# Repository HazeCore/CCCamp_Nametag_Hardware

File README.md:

# CCCamp 2023 Nametag Hardware

This is the hardware for out Nametag Badge for Chaos Communication Camp 2023. You can find more information about the Project at [https://hazeco.re/cccamp-nametag/](https://hazeco.re/cccamp-nametag/).

The state of the actual produced Hardware for CCCamp is tagged as version "v1.0".

This Repo contains a KiCAD Project, with all information to order the PCB or Modify it.

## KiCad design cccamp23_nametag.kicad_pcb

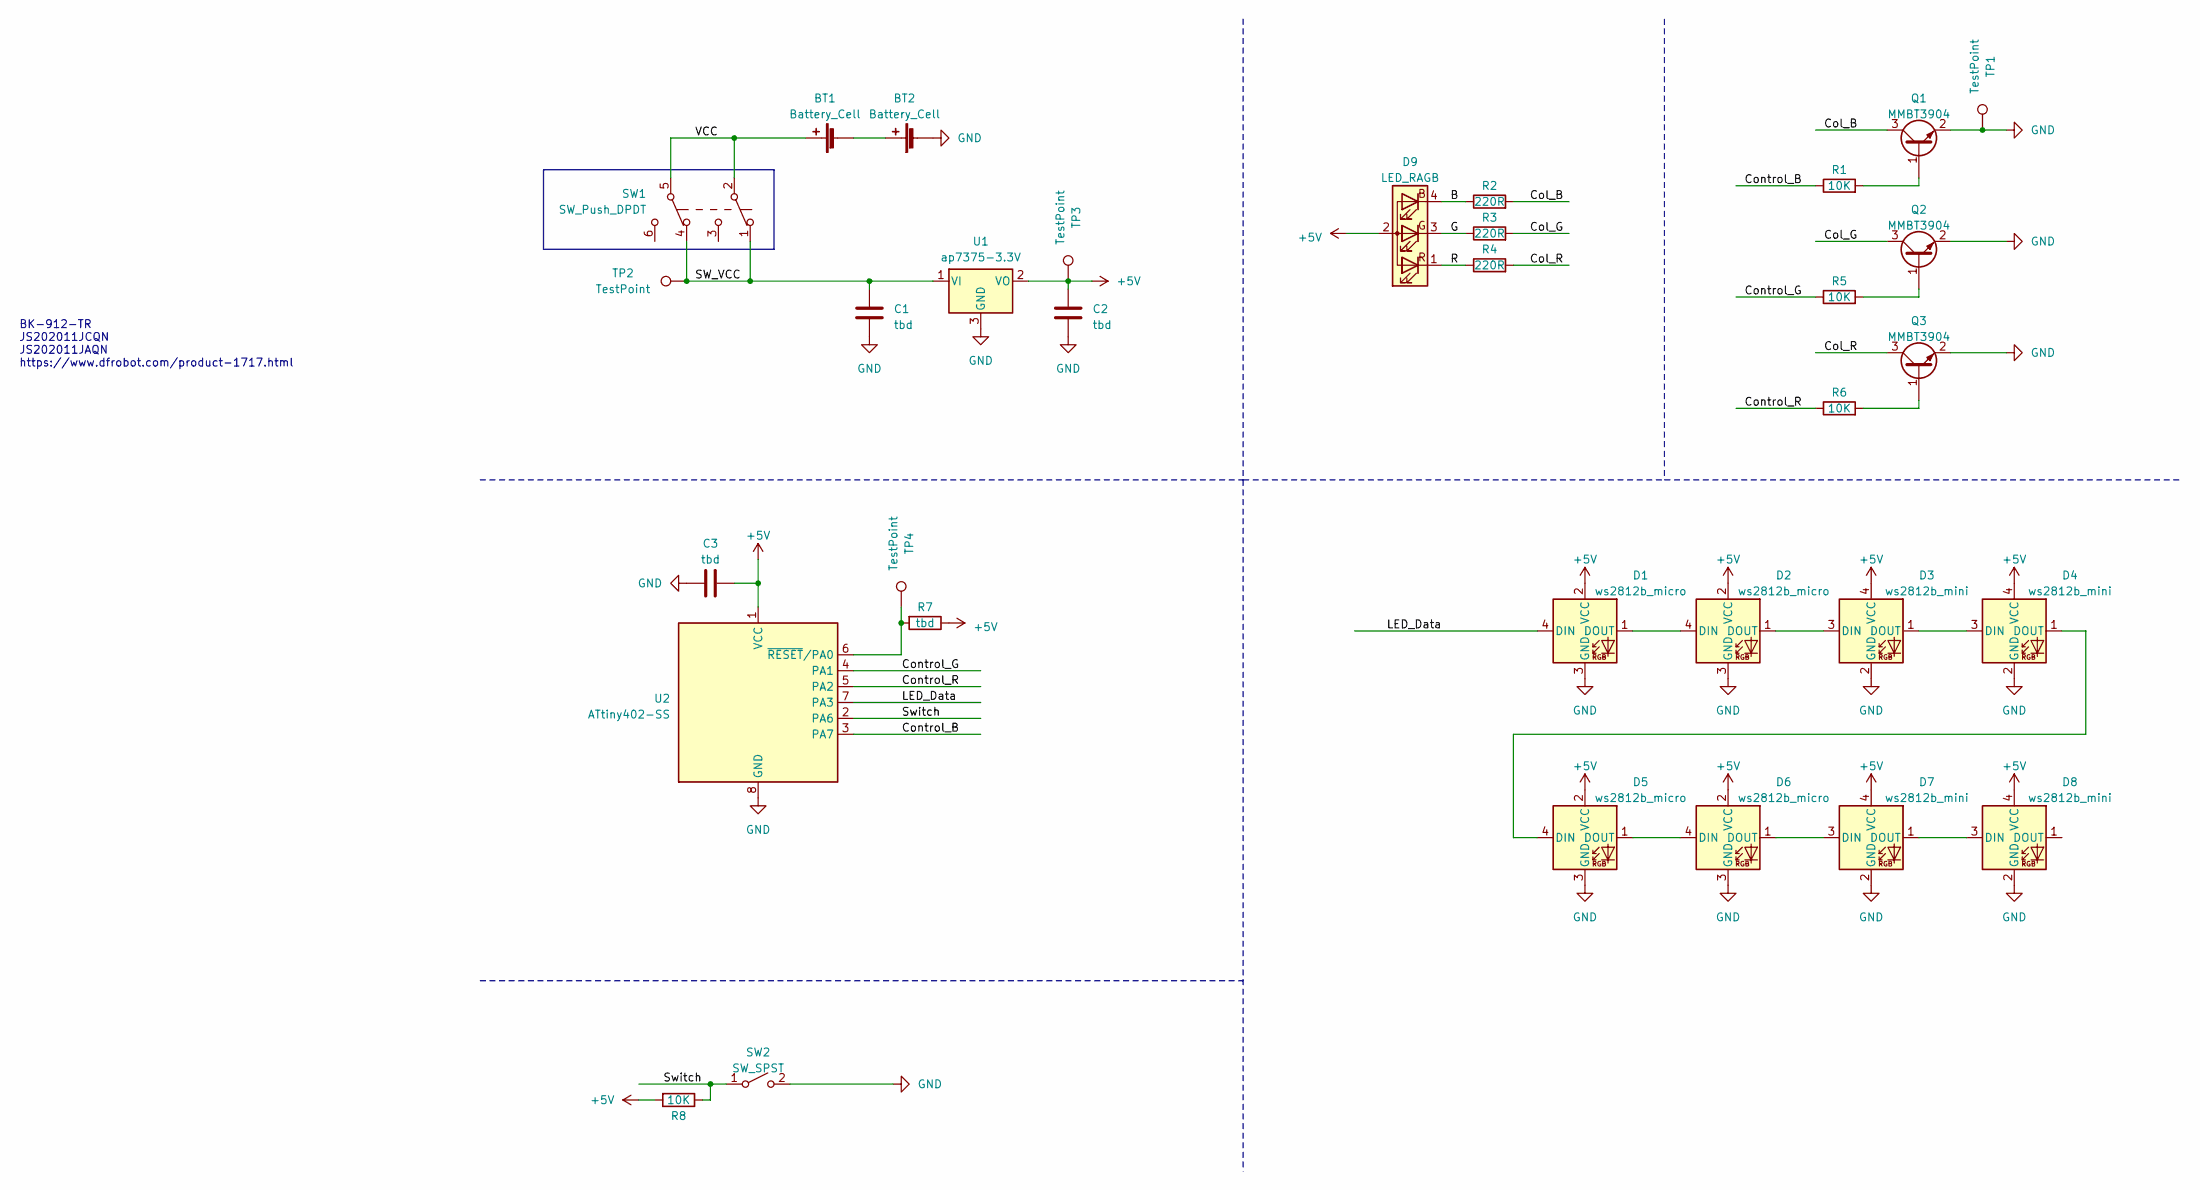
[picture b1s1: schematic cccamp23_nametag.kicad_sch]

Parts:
BT1, BT2: Battery_Cell; BatteryHolder_MPD_BC2003_1x2032
C1, C2, C3: tbd; C_0603_1608Metric
D1, D2, D5, D6: ws2812b_micro
D3, D4, D7, D8: ws2812b_mini
D9: LED_RAGB; PinHeader_1x04_P1.27mm_Vertical
Q1, Q2, Q3: MMBT3904; SOT-23
R1, R5, R6, R8: 10K; R_0603_1608Metric
R2, R3, R4: 220R; R_0603_1608Metric
R7: tbd; R_0603_1608Metric
SW1: SW_Push_DPDT; SW_DPDT_CK_JS202011JCQN
SW2: SW_SPST; pts526
TP1, TP2, TP3, TP4: TestPoint; TestPoint_Pad_D1.5mm
U1: ap7375-3.3V; SOT-23
U2: ATtiny402-SS; SOIC-8_3.9x4.9mm_P1.27mm

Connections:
+5V: C2.1, C3.2, D1.2 (VCC), D2.2 (VCC), D3.4 (VCC), D4.4 (VCC), D5.2 (VCC), D6.2 (VCC), D7.4 (VCC), D8.4 (VCC), D9.2 (A), R7.1, R8.2, TP3.1, U1.2 (VO), U2.1 (VCC)
/B: D9.4 (BK), R2.1
/Col_B: Q1.3 (C), R2.2
/Col_G: Q2.3 (C), R3.2
/Col_R: Q3.3 (C), R4.2
/Control_B: R1.1, U2.3 (PA7)
/Control_G: R5.1, U2.4 (PA1)
/Control_R: R6.1, U2.5 (PA2)
/G: D9.3 (GK), R3.1
/LED_Data: D1.4 (DIN), U2.7 (PA3)
/R: D9.1 (RK), R4.1
/SW_VCC: C1.1, SW1.1 (A), SW1.4 (A), TP2.1, U1.1 (VI)
/Switch: R8.1, SW2.1 (A), U2.2 (PA6)
/VCC: BT1.1 (+), SW1.2 (B), SW1.5 (B)
GND: BT2.2 (-), C1.2, C2.2, C3.1, D1.3 (GND), D2.3 (GND), D3.2 (GND), D4.2 (GND), D5.3 (GND), D6.3 (GND), D7.2 (GND), D8.2 (GND), Q1.2 (E), Q2.2 (E), Q3.2 (E), SW2.2 (B), TP1.1, U1.3 (GND), U2.8 (GND)
unnamed: BT1.2 (-), BT2.1 (+)
unnamed: D1.1 (DOUT), D2.4 (DIN)
unnamed: D2.1 (DOUT), D3.3 (DIN)
unnamed: D3.1 (DOUT), D4.3 (DIN)
unnamed: D4.1 (DOUT), D5.4 (DIN)
unnamed: D5.1 (DOUT), D6.4 (DIN)
unnamed: D6.1 (DOUT), D7.3 (DIN)
unnamed: D7.1 (DOUT), D8.3 (DIN)
unnamed: Q1.1 (B), R1.2
unnamed: Q2.1 (B), R5.2
unnamed: Q3.1 (B), R6.2
unnamed: R7.2, TP4.1, U2.6 (~RESET/PA0)

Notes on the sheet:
BK-912-TR JS202011JCQN JS202011JAQN https://www.dfrobot.com/product-1717.html

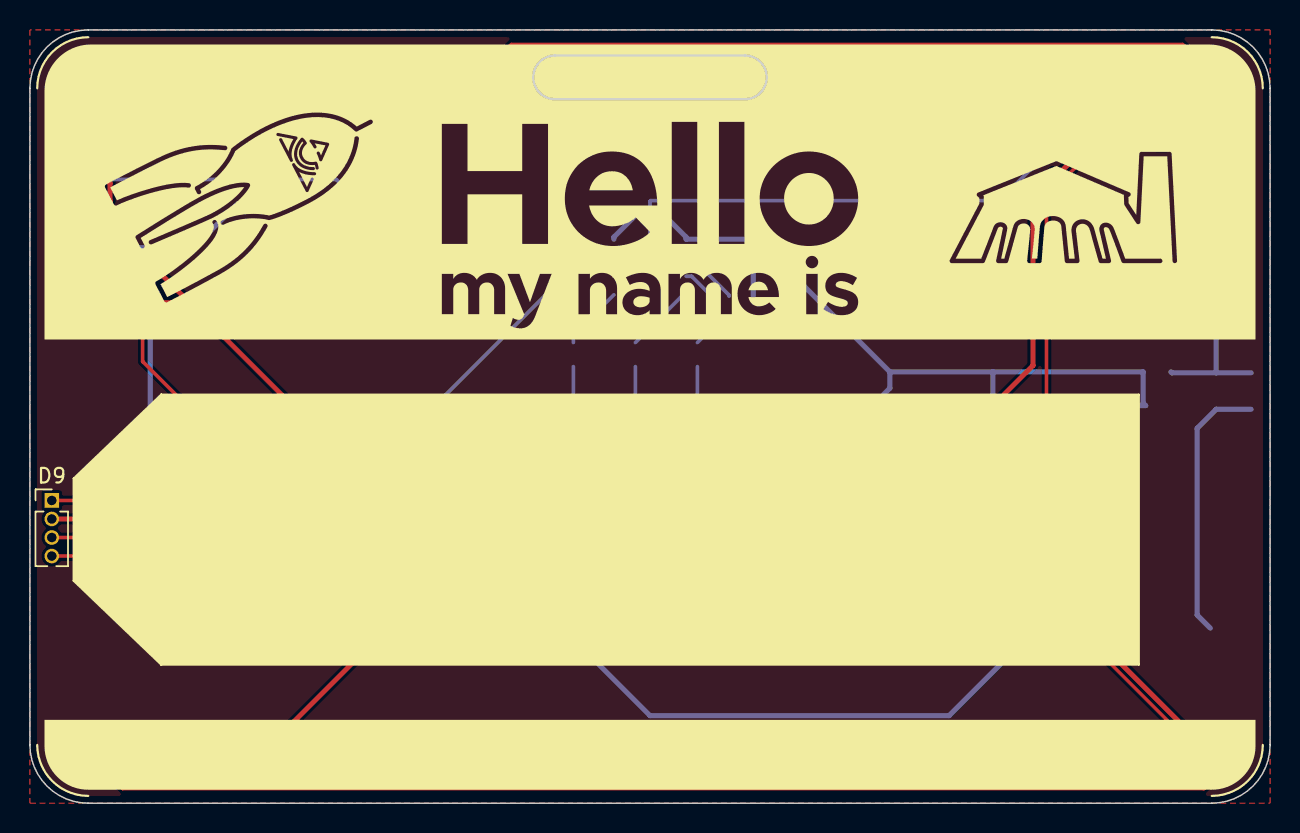
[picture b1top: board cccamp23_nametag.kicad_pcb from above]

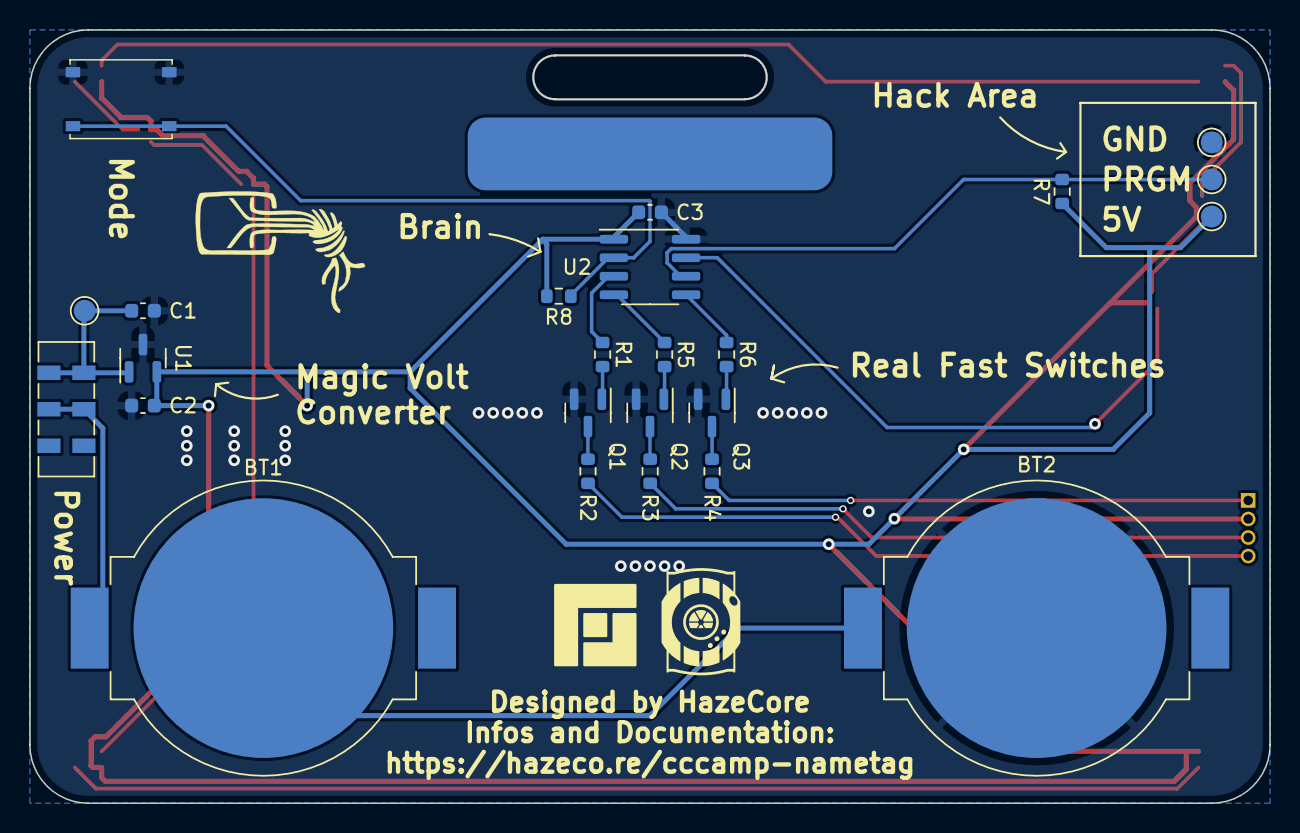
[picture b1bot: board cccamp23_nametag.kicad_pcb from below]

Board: 2 copper layers, 85.0 x 52.9 mm, 33 parts (24 on the bottom side), 27 nets.

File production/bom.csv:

Designator,Footprint,Quantity,Value,LCSC Part #
"BT1, BT2",BatteryHolder_MPD_BC2003_1x2032,2,Battery_Cell,
"C1, C2, C3, R7",0603,4,tbd,
"D1, D2, D5, D6",ws2812b_micro,4,ws2812b_micro,
"D3, D4, D7, D8",ws2812b_mini,4,ws2812b_mini,
D9,PinHeader_1x04_P1.27mm_Vertical,1,LED_RAGB,
"Q1, Q2, Q3",SOT-23,3,MMBT3904,
"R1, R5, R6, R8",0603,4,10K,
"R2, R3, R4",0603,3,220R,
SW1,SW_DPDT_CK_JS202011JCQN,1,SW_Push_DPDT,
SW2,pts526,1,SW_SPST,
"TP1, TP2, TP3, TP4",TestPoint_Pad_D1.5mm,4,TestPoint,
U1,SOT-23,1,ap7375-3.3V,
U2,SOIC-8_3.9x4.9mm_P1.27mm,1,ATtiny402-SS,

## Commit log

2023-07-17 final1
2023-11-15 updated gitignore
2023-11-15 update schematic
2023-11-15 apply .gitignore
2023-11-15 add Readme
